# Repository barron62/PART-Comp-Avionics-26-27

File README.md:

# PART-Avionics-26-27
PART (Purdue Aerial Robotics Team) PCBs accompanying embedded code
Custom PCBS:
 PDU (power distribution unit)
 Pixhawk Carrier Board
 Battery Bleed Board
 Sensor Board
 Thrust Stand Board

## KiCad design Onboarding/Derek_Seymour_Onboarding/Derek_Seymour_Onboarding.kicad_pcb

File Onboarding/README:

Comp Avionics Onboarding Project

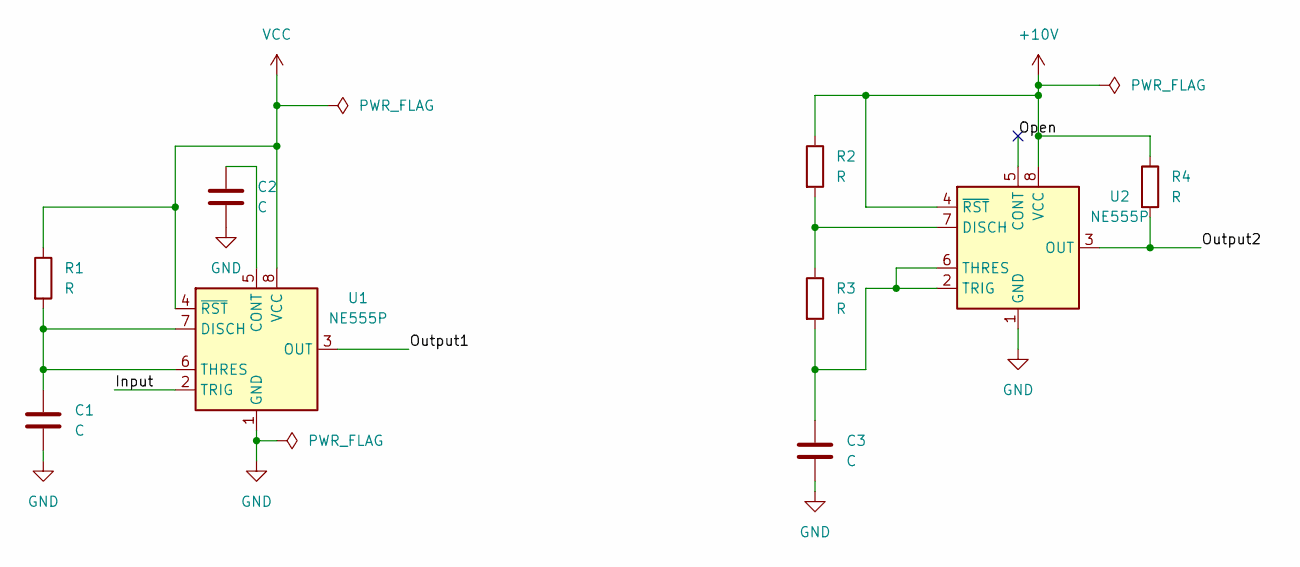
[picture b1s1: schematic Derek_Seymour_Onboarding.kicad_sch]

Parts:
C1, C2, C3: C; C_Elec_4x5.4
R1, R2: R; DIP-8_W7.62mm
R3, R4: R; R_0805_2012Metric
U1, U2: NE555P; DIP-8_W7.62mm

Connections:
+10V: R2.1, R4.1, U2.4 (~RST), U2.8 (VCC)
/Input: U1.2 (TRIG)
/Open: U2.5 (CONT)
/Output: U1.3 (OUT)
/Output2: R4.2, U2.3 (OUT)
GND: C1.2, C2.2, C3.2, U1.1 (GND), U2.1 (GND)
unnamed: C2.1, U1.5 (CONT)
unnamed: C1.1, R1.2, U1.6 (THRES), U1.7 (DISCH)
unnamed: R2.2, R3.1, U2.7 (DISCH)
unnamed: C3.1, R3.2, U2.2 (TRIG), U2.6 (THRES)
VCC: R1.1, U1.4 (~RST), U1.8 (VCC)

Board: 2 copper layers, 9 parts (0 on the bottom side), 8 nets, no tracks yet.

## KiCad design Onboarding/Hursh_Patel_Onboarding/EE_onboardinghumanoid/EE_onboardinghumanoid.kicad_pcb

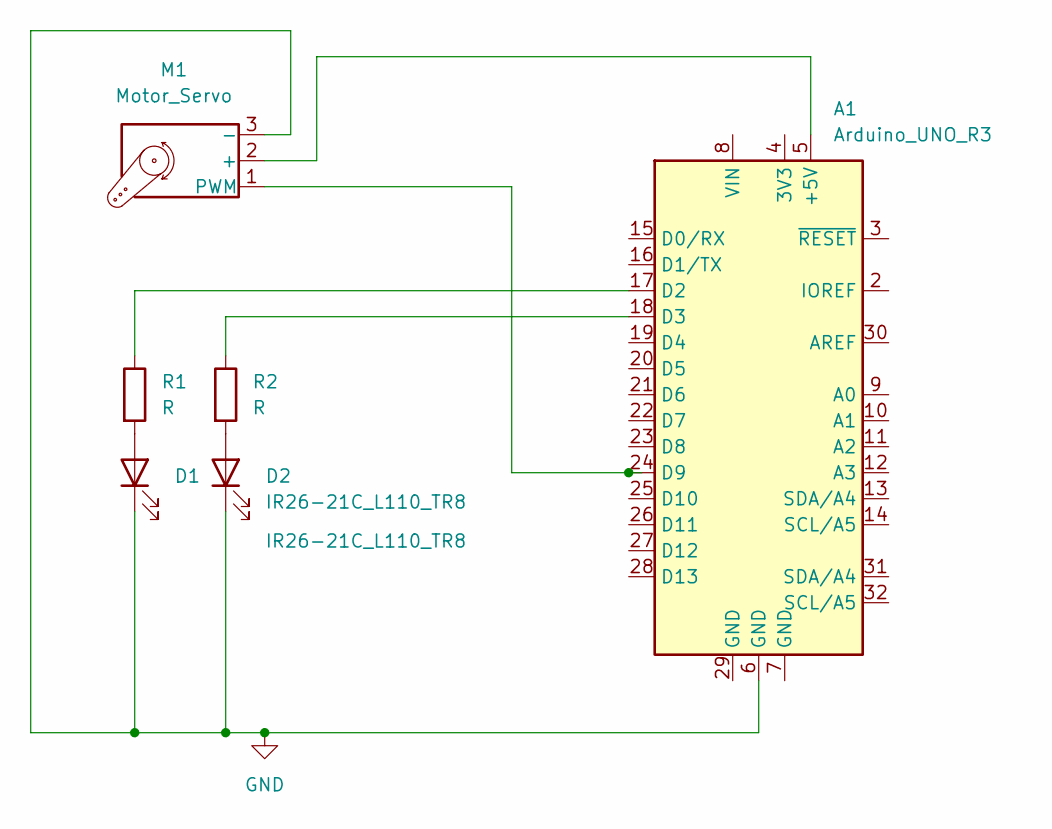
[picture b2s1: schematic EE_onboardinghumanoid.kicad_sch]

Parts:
A1: Arduino_UNO_R3
D1, D2: IR26-21C_L110_TR8; LED_D3.0mm
M1: Motor_Servo; PinHeader_1x30_P1.00mm_Horizontal
R1, R2: R; R_Axial_DIN0207_L6.3mm_D2.5mm_P7.62mm_Horizontal

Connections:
GND: A1.6 (GND), D1.1 (K), D2.1 (K), M1.3 (-)
unnamed: A1.5 (+5V), M1.2 (+)
unnamed: A1.17 (D2), R1.1
unnamed: A1.18 (D3), R2.1
unnamed: A1.24 (D9), M1.1 (PWM)
unnamed: D1.2 (A), R1.2
unnamed: D2.2 (A), R2.2

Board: 2 copper layers, 6 parts (0 on the bottom side), 7 nets, no tracks yet.

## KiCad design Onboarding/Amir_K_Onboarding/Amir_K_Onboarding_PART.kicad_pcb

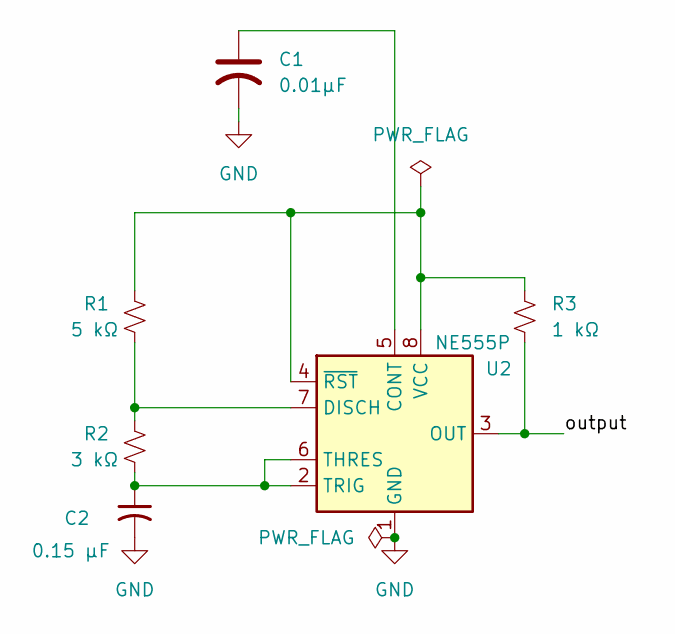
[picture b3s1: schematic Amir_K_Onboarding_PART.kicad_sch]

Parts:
C1: 0.01µF; C_1206_3216Metric
C2: 0.15 µF; C_1206_3216Metric
R1: 5 kΩ; R_1206_3216Metric
R2: 3 kΩ; R_1206_3216Metric
R3: 1 kΩ; R_1206_3216Metric
U2: NE555P; DIP-8_W7.62mm

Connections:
/output: R3.2, U2.3 (OUT)
GND: C1.2, C2.2, U2.1 (GND)
unnamed: C1.1, U2.5 (CONT)
unnamed: R1.2, R2.1, U2.7 (DISCH)
unnamed: C2.1, R2.2, U2.2 (TRIG), U2.6 (THRES)
unnamed: R1.1, R3.1, U2.4 (~RST), U2.8 (VCC)

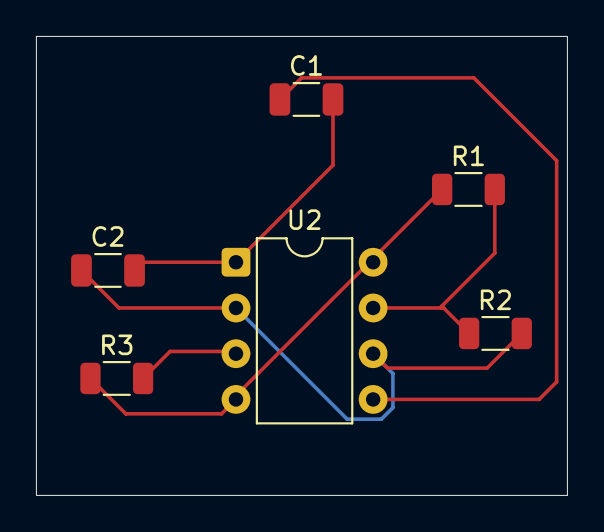
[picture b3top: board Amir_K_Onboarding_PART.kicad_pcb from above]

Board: 2 copper layers, 29.5 x 25.5 mm, 6 parts (0 on the bottom side), 6 nets.

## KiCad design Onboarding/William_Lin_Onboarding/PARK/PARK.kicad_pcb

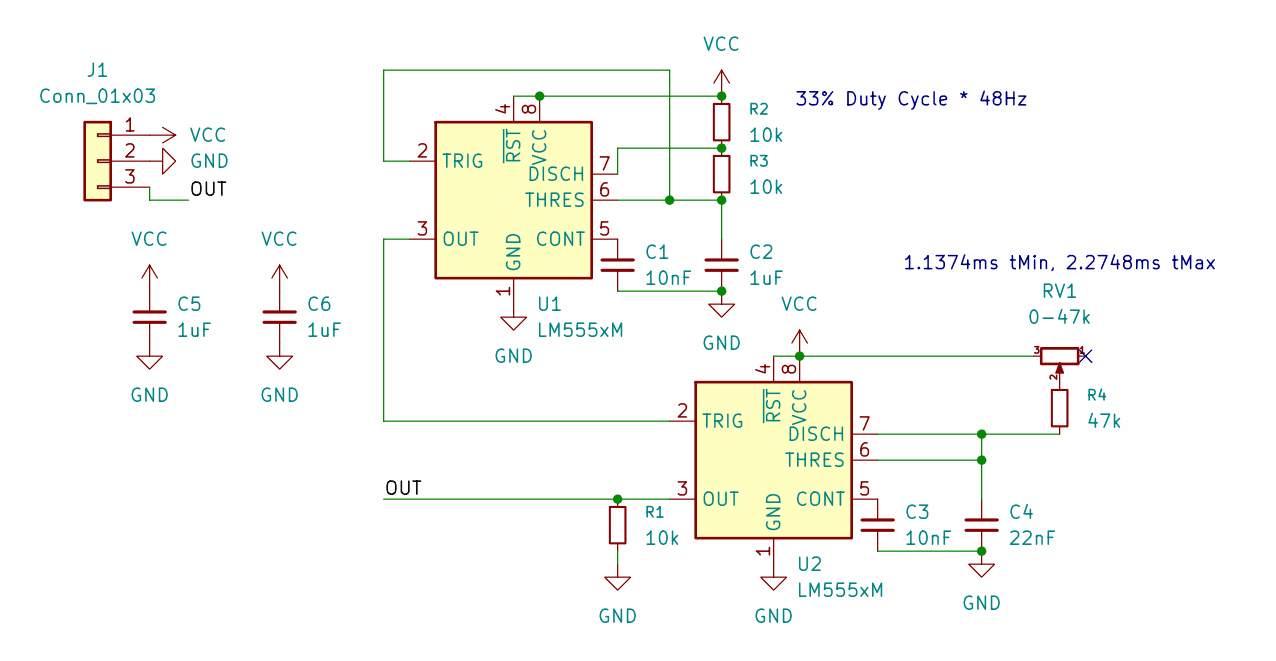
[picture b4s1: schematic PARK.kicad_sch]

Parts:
C1, C3: 10nF; C_0805_2012Metric_Pad1.18x1.45mm_HandSolder
C2, C5, C6: 1uF; C_0805_2012Metric_Pad1.18x1.45mm_HandSolder
C4: 22nF; C_0805_2012Metric_Pad1.18x1.45mm_HandSolder
J1: Conn_01x03; JST_XH_B3B-XH-AM_1x03_P2.50mm_Vertical
R1, R2, R3: 10k; R_0805_2012Metric_Pad1.20x1.40mm_HandSolder
R4: 47k; R_0805_2012Metric_Pad1.20x1.40mm_HandSolder
RV1: 0-47k; Potentiometer_Bourns_PTV09A-1_Single_Vertical
U1, U2: LM555xM; SOIC-8_3.9x4.9mm_P1.27mm

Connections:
/OUT: J1.3, R1.1, U2.3 (OUT)
GND: C1.2, C2.2, C3.2, C4.2, C5.2, C6.2, J1.2, R1.2, U1.1 (GND), U2.1 (GND)
unnamed: R4.1, RV1.2
unnamed: C1.1, U1.5 (CONT)
unnamed: R2.2, R3.1, U1.7 (DISCH)
unnamed: U1.3 (OUT), U2.2 (TRIG)
unnamed: C2.1, R3.2, U1.2 (TRIG), U1.6 (THRES)
unnamed: C3.1, U2.5 (CONT)
unnamed: C4.1, R4.2, U2.6 (THRES), U2.7 (DISCH)
VCC: C5.1, C6.1, J1.1, R2.1, RV1.3, U1.4 (~RST), U1.8 (VCC), U2.4 (~RST), U2.8 (VCC)

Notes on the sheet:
1.1374ms tMin, 2.2748ms tMax
33% Duty Cycle * 48Hz

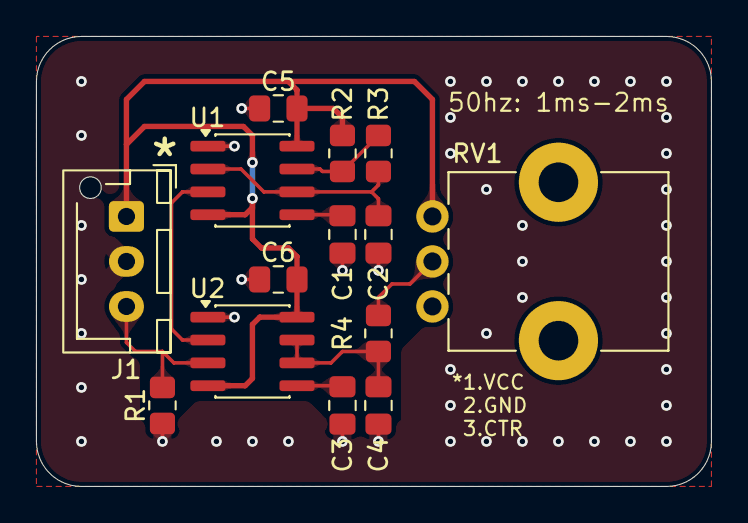
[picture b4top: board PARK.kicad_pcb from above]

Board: 2 copper layers, 37.5 x 25.0 mm, 14 parts (0 on the bottom side), 10 nets.

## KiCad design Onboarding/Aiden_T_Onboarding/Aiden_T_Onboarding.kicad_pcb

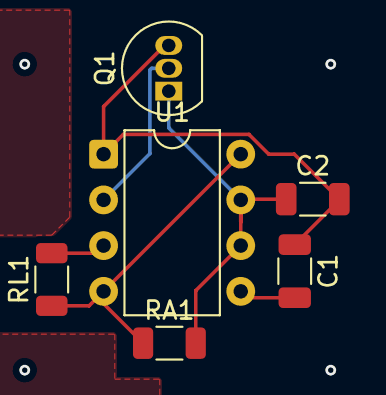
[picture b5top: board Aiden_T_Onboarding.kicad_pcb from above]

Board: 2 copper layers, 10 parts (0 on the bottom side), 6 nets.

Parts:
C1: 0.01μF; C_1206_3216Metric
C2: C; C_1206_3216Metric
H1, H2, H3, H4: MountingHole; MountingHole_4.3mm_M4
Q1: BC338; TO-92_Inline
RA1: R; R_1206_3216Metric
RL1: R; R_1206_3216Metric
U1: NE555P; DIP-8_W7.62mm

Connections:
GND: C1.1, C2.2, Q1.3 (E), U1.1 (GND)
IN: Q1.2 (B), U1.2 (TRIG)
unnamed: C2.1, Q1.1 (C), RA1.2, U1.6 (THRES), U1.7 (DISCH)
unnamed: C1.2, U1.5 (CONT)
OUT: RL1.2, U1.3 (OUT)
VCC: RA1.1, RL1.1, U1.4 (~RST), U1.8 (VCC)

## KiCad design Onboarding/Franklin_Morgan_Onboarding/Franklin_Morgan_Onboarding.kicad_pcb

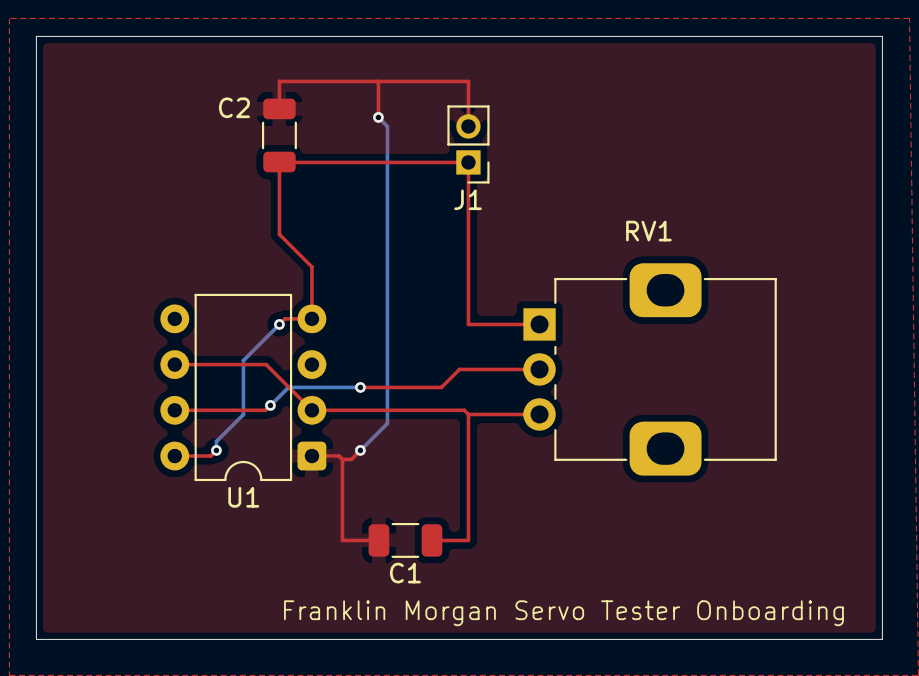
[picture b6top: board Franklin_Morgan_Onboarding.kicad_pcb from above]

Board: 2 copper layers, 47.0 x 33.5 mm, 5 parts (0 on the bottom side), 4 nets.

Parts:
C1: 0.15pF; C_1206_3216Metric
C2: 0.01uF; C_1206_3216Metric
J1: Conn_01x02_Pin; PinHeader_1x02_P2.00mm_Vertical
RV1: 1-10k; Potentiometer_Alps_RK09K_Single_Vertical
U1: NE555P; DIP-8_W7.62mm

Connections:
+5V: C2.1, J1.1, RV1.1, U1.4 (~RST), U1.8 (VCC)
GND: C1.2, C2.2, J1.2, U1.1 (GND)
unnamed: RV1.2, U1.7 (DISCH)
unnamed: C1.1, RV1.3, U1.2 (TRIG), U1.6 (THRES)

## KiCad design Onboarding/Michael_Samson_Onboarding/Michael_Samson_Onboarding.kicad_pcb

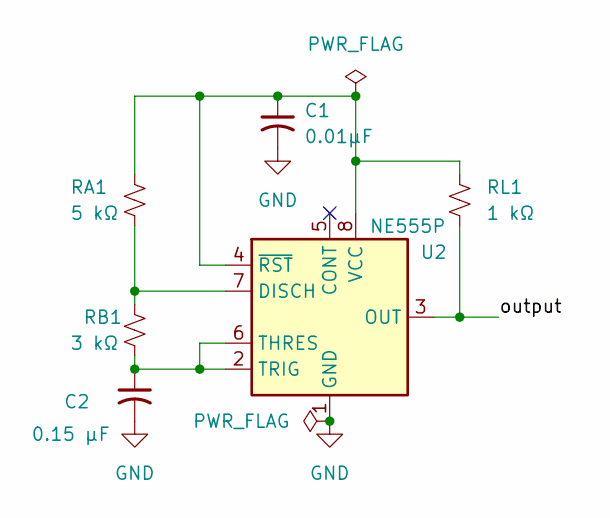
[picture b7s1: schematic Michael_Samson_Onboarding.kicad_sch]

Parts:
C1: 0.01µF; C_1206_3216Metric
C2: 0.15 µF; C_1206_3216Metric
RA1: 5 kΩ; R_1206_3216Metric
RB1: 3 kΩ; R_1206_3216Metric
RL1: 1 kΩ; R_1206_3216Metric
U2: NE555P; DIP-8_W7.62mm

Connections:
/output: RL1.2, U2.3 (OUT)
GND: C1.2, C2.2, U2.1 (GND)
unnamed: RA1.2, RB1.1, U2.7 (DISCH)
unnamed: C2.1, RB1.2, U2.2 (TRIG), U2.6 (THRES)
unnamed: C1.1, RA1.1, RL1.1, U2.4 (~RST), U2.8 (VCC)

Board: 2 copper layers, 6 parts (0 on the bottom side), 5 nets, no tracks yet.
